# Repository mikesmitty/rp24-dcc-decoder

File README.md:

# rp24-dcc-decoder
DIY DCC decoder for model railroad locomotives in an E24 form factor suitable for N scale/gauge locomotives

[Decoder identifying to JMRI](https://www.youtube.com/watch?v=m5kexSfDo3k)

## Features
- 8x MOSFET-switched functions
- 5x GPIO pins (3.3V input/output)
- Up to 0.75A motor current
- E24 form factor (approx 20mm x 9mm)
- i2s audio speaker output
- 12V nominal rail voltage (16V max)

# USB Programmer/E24 Tester

- USB-C port for easy programming and loading sound files
- Onboard LEDs for all aux outputs for simple decoder testing
- Breakout header for most E24 pins, including speaker, motor, rectified rail power, Vcc, plus all five E24 GPIO pins (Aux 3, 4, 10, 11, 12)
- Programming track input header allows for stationary decoder testing and CV programming

# RP24 Decoder Pinout
| E24 Pin | Function | GPIO Pin |
| --- | --- | --- |
| 1 | Speaker- | USB D- |
| 2 | Speaker+ | USB D+ |
| 3 | GND | GND |
| 4-5 | Motor- | N/A |
| 6-7 | Motor+ | N/A |
| 8 | Cap+ | GPIO20 |
| 9 | Lamp Front | GPIO6 (MOSFET) |
| 10 | Lamp Rear | GPIO7 (MOSFET) |
| 11 | AUX1 | GPIO8 (MOSFET) |
| 12 | AUX2 | GPIO5 (MOSFET) |
| 13 | AUX8 | GPIO4 (MOSFET) |
| 14 | AUX7 | GPIO3 (MOSFET) |
| 15 | AUX6 | GPIO9 (MOSFET) |
| 16 | AUX5 | GPIO2 (MOSFET) |
| 17 | U+ | DC Rail Voltage |
| 18 | Vcc | 3.3V |
| 19 | AUX10 | GPIO10 |
| 20 | AUX4 | GPIO13 |
| 21 | AUX3 | GPIO14 |
| 22 | GND | GND |
| 23 | AUX11 | GPIO0 |
| 24 | AUX12 | GPIO1 |
| N/A | Motor Driver A | GPIO25 |
| N/A | Motor Driver B | GPIO26 |
| N/A | Back EMF A | GPIO28 |
| N/A | Back EMF B | GPIO29 |
| N/A | DCC signal Left Rail | GPIO21 |
| N/A | DCC signal Right Rail | GPIO27 |
| N/A | RailCom Out | GPIO11 |
| N/A | Status LED | GPIO19 |
| N/A | i2s DIN | GPIO22 |
| N/A | i2s BCLK | GPIO23 |
| N/A | i2s LRCLK | GPIO24 |
| N/A | Charge external keepalive capacitor (PWM at very low duty cycle only) | GPIO20 |

# E24 Receiver/Wire Breakout Board

## Receiver Board Solder Pads
| E24 Pin | Function | Label |
| --- | --- | --- |
| 1 | Speaker- | SPK |
| 2 | Speaker+ | SPK |
| 3 | GND | G |
| 4-5 | Motor- | - MOTOR + |
| 6-7 | Motor+ | - MOTOR + |
| 8 | External Capacitor+ | C |
| 9 | Lamp Front | F LAMP R |
| 10 | Lamp Rear | F LAMP R |
| 11 | AUX1 | 1 |
| 12 | AUX2 | 2 |
| 17 | DC Rail Voltage | RV |
| 18 | Microcontroller Voltage Output | Vcc |
| 19 | AUX10 | 10 |
| 20 | AUX4 | 4 |
| 21 | AUX3 | 3 |
| 22 | GND | G |
| 23 | AUX11 | 11 |
| 24 | AUX12 | 12 |

Inspired by the rp2040-decoder project by gab-k: https://github.com/gab-k/RP2040-Decoder

## Reference:
### E24
- RCD-124 (German): https://normen.railcommunity.de/RCD-124.pdf
- https://dccwiki.com/Locomotive_Interface/E24
### RailCom
- [NMRA S-9.3.2, Section 2](https://www.nmra.org/sites/default/files/s-9.3.2_2012_12_10.pdf)
- Example RailCom transmitter circuit: [CircuitJS](https://www.falstad.com/circuit/circuitjs.html?ctz=CQAgjCAMB0l3BWcMBMcUHYMGZIA4UA2ATmIxAUgoqoQFMBaMMAKABdkUAWEFbkYoSp8eVJr2h9CKBIS6E8kQrgyRsjPCAYZJM4vgxCU2E90bNecEABM6AMwCGAVwA2bdgMO8MKTj0y+YhDY0GB4XAgmkFwoYAhg0sRaKLrSsvKKypCq6gyaaFS2jq7uAE5+4EIVIlC8KCzlgsI+IHiC3oEgCnAsAEoVzL5gkPxcmlRUXFQh2LUT0Ageg9MIQ2E82Ku1EDDZxG1cU-FywwhJMMwI8iRoMXKr8paF9s5uSyMbW2SEIJudO7AMPtiIc0DIwAVsD9hFYiq8yhU-uAIStOt1ICwAMqtdoBECGfItKgQRwuADOdFq9QA5viFLw8JoCb8oXMWLTmOFfvTOTwphMoCxsKoKvIeMsQGLfmyAO7VfjDfgyaEsOVNXhTARVPEYtXalrfDqCuWK8UQrXE826i2VKjqtDjVU2wZ0zQu63Ml3M5XG6qMxFba2GqGaQ3831hqymyVWa3R8PRpFx9Ysn4Q7C+Ewqk3GTOs9O+KVB81S4jmrMR8us4OsuO5yVyZFoBuiJ3xxtlwuNjHC4kfJsDKqzCZO9UusdVDFAA)

View this project on [CADLAB.io](https://cadlab.io/project/28797).

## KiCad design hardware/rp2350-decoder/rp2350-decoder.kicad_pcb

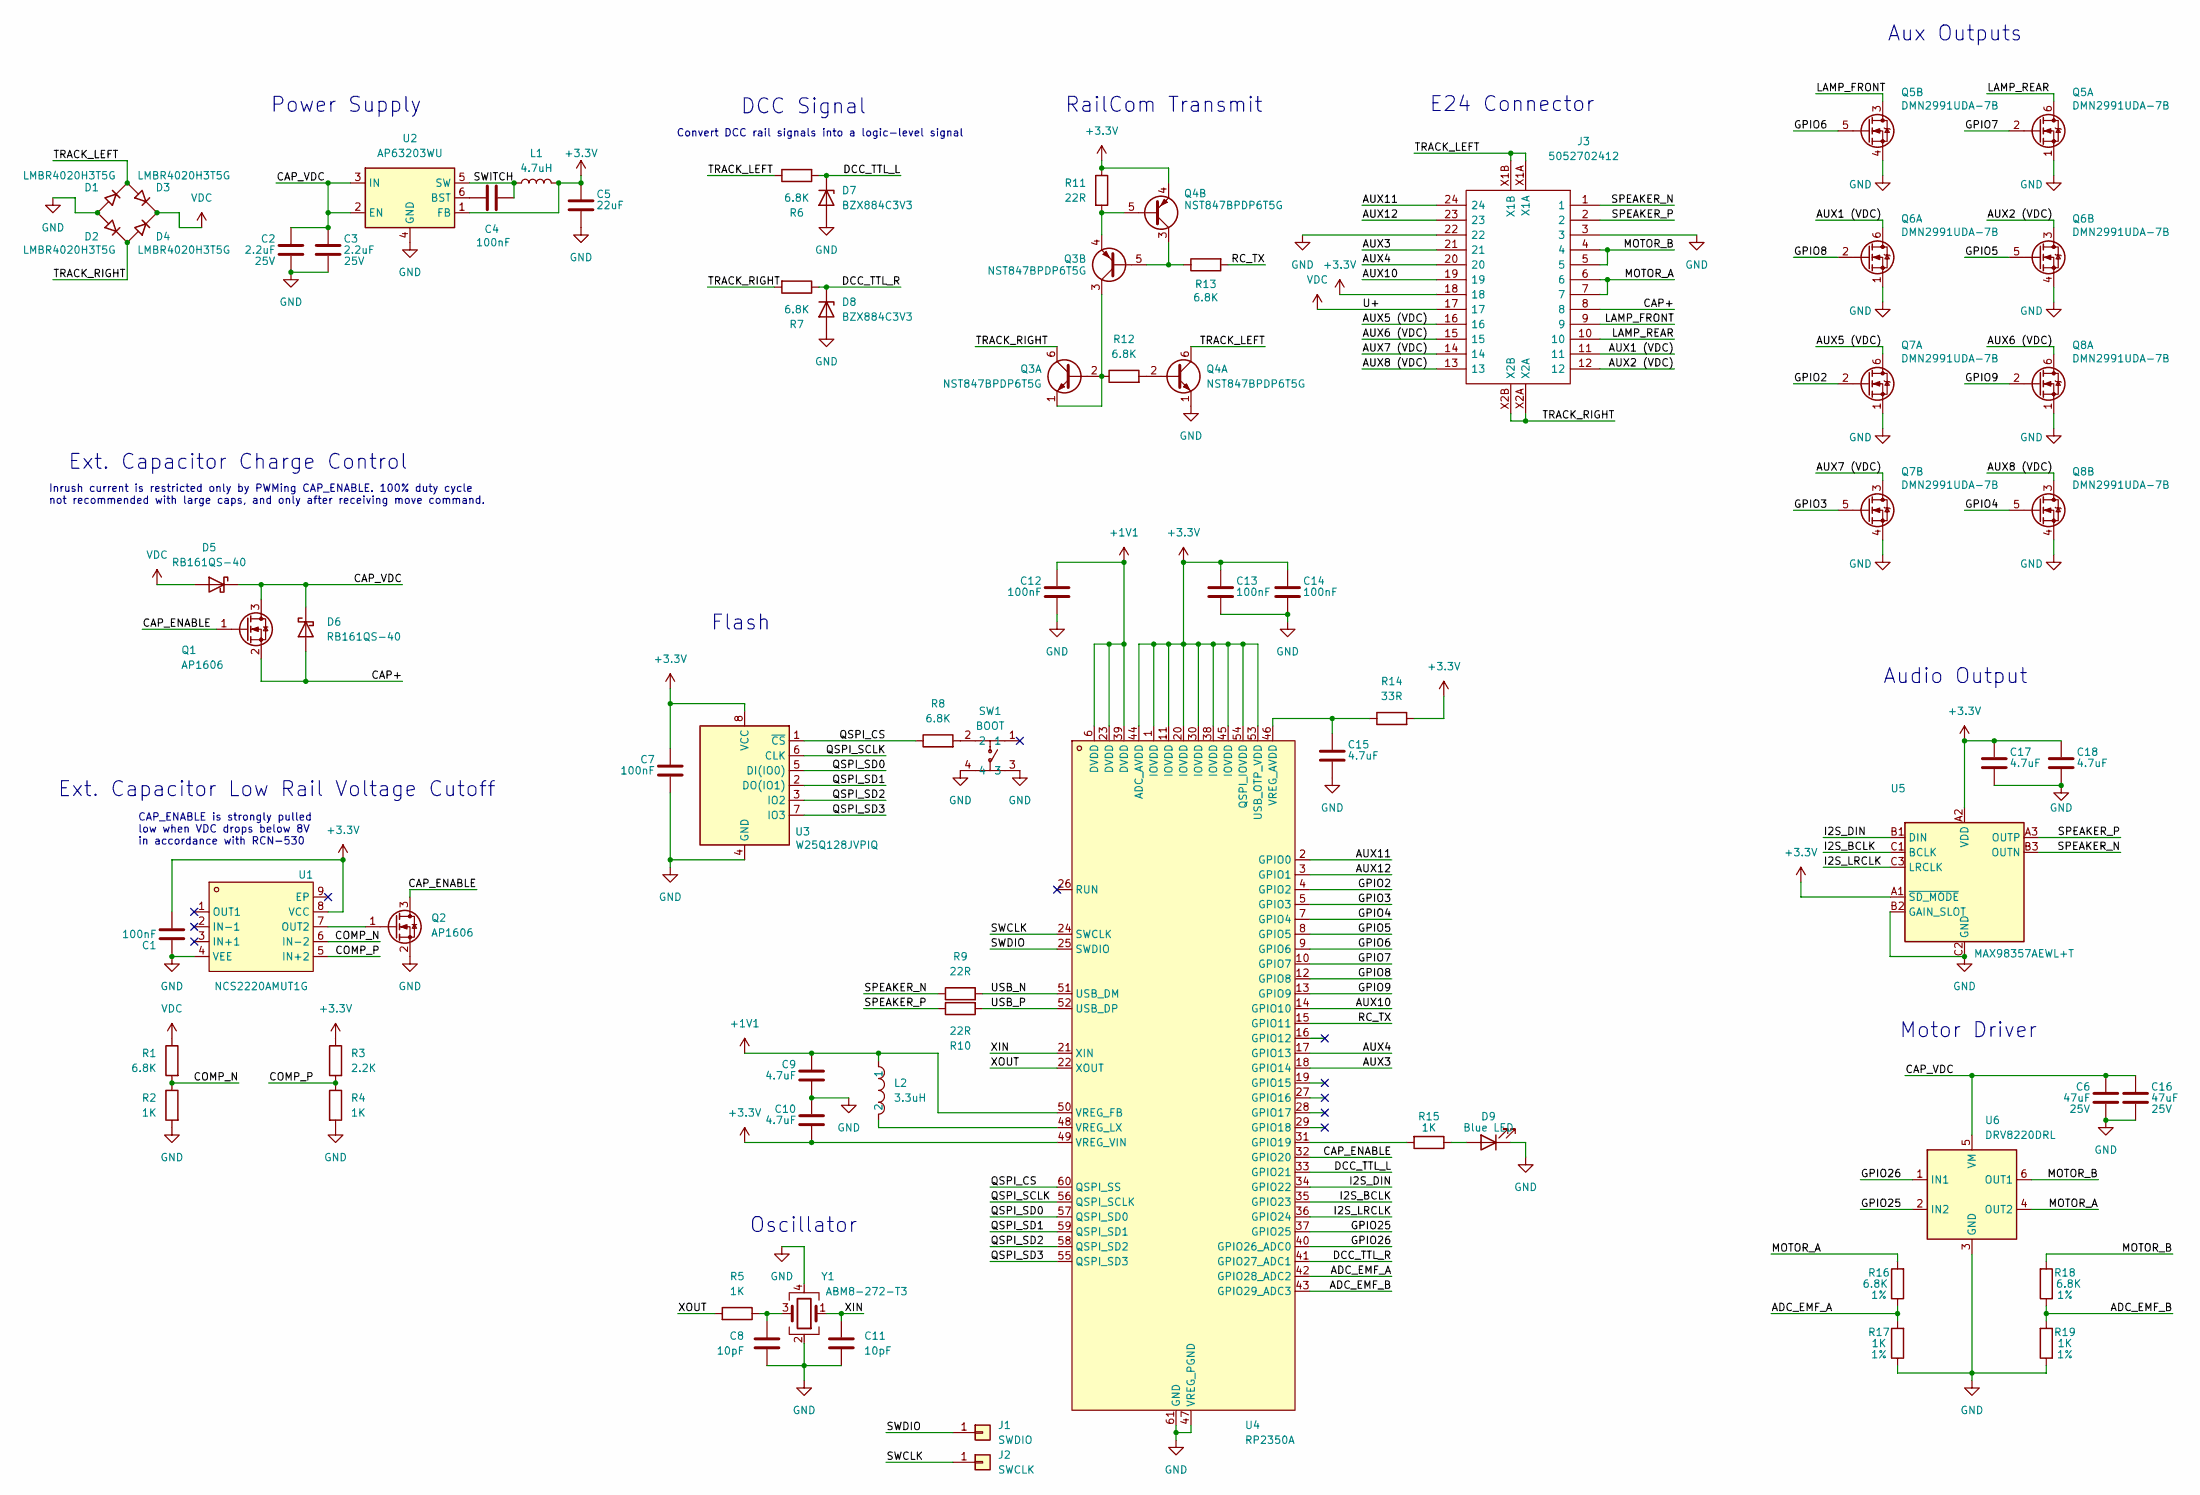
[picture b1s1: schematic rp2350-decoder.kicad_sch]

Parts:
C1, C4, C7, C12, C13, C14: 100nF; C_0201_0603Metric; LCSC C49062
C2, C3: 2.2uF; C_0402_1005Metric; Voltage 25V; LCSC C159814
C5: 22uF; C_0603_1608Metric; LCSC C86295
C6, C16: 47uF; C_1206_3216Metric; Voltage 25V; LCSC C22367835
C8, C11: 10pF; C_0201_0603Metric; LCSC C384956
C9, C10, C15, C17, C18: 4.7uF; C_0201_0603Metric; LCSC C335103
D1, D2, D3, D4: LMBR4020H3T5G; U-DFN1608-2_L1.6-W0.8-RD; LCSC C2852608
D5, D6: RB161QS-40; DIO-SMD_L1.0-W0.6-P0.65-RD; LCSC C5563750
D7, D8: BZX884C3V3; DFN1006-2L-RD; LCSC C7529009
D9: Blue LED; LED_0402_1005Metric; LCSC C130724
J1: SWDIO; Pogo Pad 0.8mm
J2: SWCLK; Pogo Pad 0.8mm
J3: 5052702412; CONN-SMD_5052702412; LCSC C724151
L1: 4.7uH; IND-SMD_L2.5-W2.0-VLS252012CX-150M; LCSC C5832360
L2: 3.3uH; L_pol_2016; LCSC C42411119
Q1, Q2: AP1606; Diodes_DFN1006-3; LCSC C2849580
Q3, Q4: NST847BPDP6T5G; SOT-963; LCSC C896443
Q5, Q6, Q7, Q8: DMN2991UDA-7B; X2-DFN0806-6_L0.8-W0.6_X2-DFN0806-6; LCSC C2937136
R1, R6, R7, R8, R12, R13: 6.8K; R_0201_0603Metric; LCSC C423451
R2, R4, R5, R15: 1K; R_0201_0603Metric; LCSC C270365
R3: 2.2K; R_0201_0603Metric; LCSC C473534
R9, R10, R11: 22R; R_0201_0603Metric; LCSC C270355
R14: 33R; R_0201_0603Metric; LCSC C423356
R16, R18: 6.8K; R_0201_0603Metric; Tolerance 1%; LCSC C423451
R17, R19: 1K; R_0201_0603Metric; Tolerance 1%; LCSC C270365
SW1: BOOT; SW-SMD_4P-L2.6-W1.6-P0.75-LS3.0; LCSC C913778
U1: NCS2220AMUT1G; DFN-8_L1.6-W1.6-P0.40-BL-EP; LCSC C464059
U2: AP63203WU; TSOT-26_L2.9-W1.6-P0.95-LS2.8-BL; LCSC C780769
U3: W25Q128JVPIQ; WSON-8-1EP_6x5mm_P1.27mm_EP3.4x4.3mm; LCSC C190862
U4: RP2350A; QFN-60_L7.0-W7.0-P0.40-TL-EP3.4; LCSC C42411118
U5: MAX98357AEWL+T; WLP-9_L1.4-W1.3-P0.40-R3-C3-BR; LCSC C2682619
U6: DRV8220DRL; SOT-563; LCSC C3681351
Y1: ABM8-272-T3; Crystal_SMD_3225-4Pin_3.2x2.5mm; LCSC C20625731

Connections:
+1V1: C9.1, C12.1, L2.1, U4.6 (DVDD), U4.23 (DVDD), U4.39 (DVDD), U4.50 (VREG_FB)
+3.3V: C1.2, C5.1, C7.1, C10.2, C13.1, C14.1, C17.1, C18.1, J3.18, L1.2, Q4.4 (E2), R3.1, R11.1, R14.2, U1.8 (VCC), U2.1 (FB), U3.8 (VCC), U4.1 (IOVDD), U4.11 (IOVDD), U4.20 (IOVDD), U4.30 (IOVDD), U4.38 (IOVDD), U4.44 (ADC_AVDD), U4.45 (IOVDD), U4.49 (VREG_VIN), U4.53 (USB_OTP_VDD), U4.54 (QSPI_IOVDD), U5.A1 (~SD_MODE), U5.A2 (VDD)
/ADC_EMF_A: R16.1, R17.2, U4.42 (GPIO28_ADC2)
/ADC_EMF_B: R18.1, R19.2, U4.43 (GPIO29_ADC3)
/AUX1 (VDC): J3.11, Q6.6 (D1)
/AUX2 (VDC): J3.12, Q6.3 (D2)
/AUX3: J3.21, U4.18 (GPIO14)
/AUX4: J3.20, U4.17 (GPIO13)
/AUX5 (VDC): J3.16, Q7.6 (D1)
/AUX6 (VDC): J3.15, Q8.6 (D1)
/AUX7 (VDC): J3.14, Q7.3 (D2)
/AUX8 (VDC): J3.13, Q8.3 (D2)
/AUX10: J3.19, U4.14 (GPIO10)
/AUX11: J3.24, U4.2 (GPIO0)
/AUX12: J3.23, U4.3 (GPIO1)
/CAP+: D6.2 (A), J3.8, Q1.2 (S)
/CAP_ENABLE: Q1.1 (G), Q2.3 (D), U4.32 (GPIO20)
/CAP_VDC: C2.1, C3.1, C6.1, C16.1, D5.1 (K), D6.1 (K), Q1.3 (D), U2.2 (EN), U2.3 (IN), U6.5 (VM)
/COMP_N: R1.2, R2.1, U1.6 (IN−2)
/COMP_P: R3.2, R4.1, U1.5 (IN+2)
/DCC_TTL_L: D7.1 (K), R6.2, U4.33 (GPIO21)
/DCC_TTL_R: D8.1 (K), R7.1, U4.41 (GPIO27_ADC1)
/GPIO2: Q7.2 (G1), U4.4 (GPIO2)
/GPIO3: Q7.5 (G2), U4.5 (GPIO3)
/GPIO4: Q8.5 (G2), U4.7 (GPIO4)
/GPIO5: Q6.5 (G2), U4.8 (GPIO5)
/GPIO6: Q5.5 (G2), U4.9 (GPIO6)
/GPIO7: Q5.2 (G1), U4.10 (GPIO7)
/GPIO8: Q6.2 (G1), U4.12 (GPIO8)
/GPIO9: Q8.2 (G1), U4.13 (GPIO9)
/GPIO25: U4.37 (GPIO25), U6.2 (IN2)
/GPIO26: U4.40 (GPIO26_ADC0), U6.1 (IN1)
/I2S_BCLK: U4.35 (GPIO23), U5.C1 (BCLK)
/I2S_DIN: U4.34 (GPIO22), U5.B1 (DIN)
/I2S_LRCLK: U4.36 (GPIO24), U5.C3 (LRCLK)
/LAMP_FRONT: J3.9, Q5.3 (D2)
/LAMP_REAR: J3.10, Q5.6 (D1)
/MOTOR_A: J3.6, J3.7, R16.2, U6.4 (OUT2)
/MOTOR_B: J3.4, J3.5, R18.2, U6.6 (OUT1)
/QSPI_CS: R8.1, U3.1 (~CS), U4.60 (QSPI_SS)
/QSPI_SCLK: U3.6 (CLK), U4.56 (QSPI_SCLK)
/QSPI_SD0: U3.5 (DI(IO0)), U4.57 (QSPI_SD0)
/QSPI_SD1: U3.2 (DO(IO1)), U4.59 (QSPI_SD1)
/QSPI_SD2: U3.3 (IO2), U4.58 (QSPI_SD2)
/QSPI_SD3: U3.7 (IO3), U4.55 (QSPI_SD3)
/RC_TX: R13.2, U4.15 (GPIO11)
/SPEAKER_N: J3.1, R9.1, U5.B3 (OUTN)
/SPEAKER_P: J3.2, R10.1, U5.A3 (OUTP)
/SWCLK: J2.1, U4.24 (SWCLK)
/SWDIO: J1.1, U4.25 (SWDIO)
/SWITCH: C4.2, L1.1, U2.5 (SW)
/TRACK_LEFT: D1.1 (K), D3.2 (A), J3.X1A, J3.X1B, Q4.6 (C1), R6.1
/TRACK_RIGHT: D2.1 (K), D4.2 (A), J3.X2A, J3.X2B, Q3.6 (C1), R7.2
/USB_N: R9.2, U4.51 (USB_DM)
/USB_P: R10.2, U4.52 (USB_DP)
/XIN: C11.1, U4.21 (XIN), Y1.1
/XOUT: R5.2, U4.22 (XOUT)
GND: C1.1, C2.2, C3.2, C5.2, C6.2, C7.2, C8.2, C9.2, C10.1, C11.2, C12.2, C13.2, C14.2, C15.2, C16.2, C17.2, C18.2, D1.2 (A), D2.2 (A), D7.2 (A), D8.2 (A), D9.1 (K), J3.3, J3.22, Q2.2 (S), Q4.1 (E1), Q5.1 (S1), Q5.4 (S2), Q6.1 (S1), Q6.4 (S2), Q7.1 (S1), Q7.4 (S2), Q8.1 (S1), Q8.4 (S2), R2.2, R4.2, R17.1, R19.1, SW1.3, SW1.4, U1.4 (VEE), U2.4 (GND), U3.4 (GND), U3.9 (GND), U4.47 (VREG_PGND), U4.61 (GND), U5.B2 (GAIN_SLOT), U5.C2 (GND), U6.3 (GND), Y1.2, Y1.4
unnamed: C8.1, R5.1, Y1.3
unnamed: D9.2 (A), R15.1
unnamed: Q2.1 (G), U1.7 (OUT2)
unnamed: Q3.1 (E1), Q3.2 (B1), Q3.3 (C2), R12.1
unnamed: Q3.5 (B2), Q4.3 (C2), R13.1
unnamed: Q3.4 (E2), Q4.5 (B2), R11.2
unnamed: Q4.2 (B1), R12.2
unnamed: R8.2, SW1.2
unnamed: C4.1, U2.6 (BST)
unnamed: R15.2, U4.31 (GPIO19)
unnamed: C15.1, R14.1, U4.46 (VREG_AVDD)
unnamed: L2.2, U4.48 (VREG_LX)
VDC: D3.1 (K), D4.1 (K), D5.2 (A), J3.17, R1.1

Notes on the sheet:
Inrush current is restricted only by PWMing CAP_ENABLE. 100% duty cycle not recommended with large caps, and only after receiving move command.
CAP_ENABLE is strongly pulled low when VDC drops below 8V in accordance with RCN-530
Aux Outputs
RailCom Transmit
Convert DCC rail signals into a logic-level signal
Motor Driver
Oscillator
Power Supply
Flash
Ext. Capacitor Low Rail Voltage Cutoff
Ext. Capacitor Charge Control
Audio Output
E24 Connector
DCC Signal

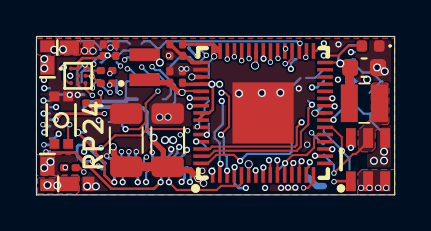
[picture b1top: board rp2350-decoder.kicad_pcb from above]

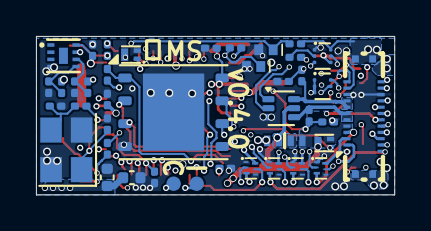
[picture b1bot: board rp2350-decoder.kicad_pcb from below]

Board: 6 copper layers, 19.9 x 8.8 mm, 67 parts (43 on the bottom side), 71 nets.

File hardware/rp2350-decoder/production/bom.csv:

Comment,Designator,Footprint,LCSC
LMBR4020H3T5G,"D1,D2,D3,D4",rp2350-decoder:U-DFN1608-2_L1.6-W0.8-RD,C2852608
MAX98357AEWL+T,U5,rp2350-decoder:WLP-9_L1.4-W1.3-P0.40-R3-C3-BR,C2682619
100nF,"C1,C4,C7,C12,C13,C14,C19",rp2350-decoder:C_0201_0603Metric,C49062
1K,"R2,R4,R5,R15,R17,R19",rp2350-decoder:R_0201_0603Metric,C270365
6.8K,"R1,R6,R7,R8,R12,R13,R16,R18",rp2350-decoder:R_0201_0603Metric,C423451
AP63203WU,U2,rp2350-decoder:TSOT-26_L2.9-W1.6-P0.95-LS2.8-BL,C780769
AP1606,"Q1,Q2",rp2350-decoder:Diodes_DFN1006-3,C2849580
BZX884C3V3,"D7,D8",rp2350-decoder:DFN1006-2L-RD,C7529009
NST847BPDP6T5G,"Q3,Q4",rp2350-decoder:SOT-963,C896443
BOOT,SW1,rp2350-decoder:SW-SMD_4P-L2.6-W1.6-P0.75-LS3.0,C913778
22R,"R9,R10,R11",rp2350-decoder:R_0201_0603Metric,C270355
2.2K,R3,rp2350-decoder:R_0201_0603Metric,C473534
DMN2991UDA-7B,"Q5,Q6,Q7,Q8",rp2350-decoder:X2-DFN0806-6_L0.8-W0.6_X2-DFN0806-6,C2937136
3.3uH,L2,rp2350-decoder:L_pol_2016,C42411119
4.7uF,"C9,C10,C15,C17,C18",rp2350-decoder:C_0201_0603Metric,C335103
RB161QS-40,"D5,D6",rp2350-decoder:DIO-SMD_L1.0-W0.6-P0.65-RD,C5563750
MD9927,U6,rp2350-decoder:WDFN-8_L2.0-W2.0-P0.50-BL-EP,C2684662
47uF,C16,rp2350-decoder:C_1206_3216Metric,C22367835
10pF,"C8,C11",rp2350-decoder:C_0201_0603Metric,C384956
5052702412,J3,rp2350-decoder:CONN-SMD_5052702412,C724151
W25Q128JVPIQ,U3,rp2350-decoder:WSON-8-1EP_6x5mm_P1.27mm_EP3.4x4.3mm,C190862
4.7uH,L1,rp2350-decoder:IND-SMD_L2.5-W2.0-VLS252012CX-150M,C5832360
ABM8-272-T3,Y1,rp2350-decoder:Crystal_SMD_3225-4Pin_3.2x2.5mm,C20625731
NCS2220AMUT1G,U1,rp2350-decoder:DFN-8_L1.6-W1.6-P0.40-BL-EP,C464059
2.2uF,"C2,C3",rp2350-decoder:C_0402_1005Metric,C159814
100uF,C6,rp2350-decoder:C_1206_3216Metric,C15008
33R,R14,rp2350-decoder:R_0201_0603Metric,C423356
Blue LED,D9,rp2350-decoder:LED_0402_1005Metric,C130724
RP2350A,U4,rp2350-decoder:QFN-60_L7.0-W7.0-P0.40-TL-EP3.4,C42411118
22uF,C5,rp2350-decoder:C_0603_1608Metric,C86295

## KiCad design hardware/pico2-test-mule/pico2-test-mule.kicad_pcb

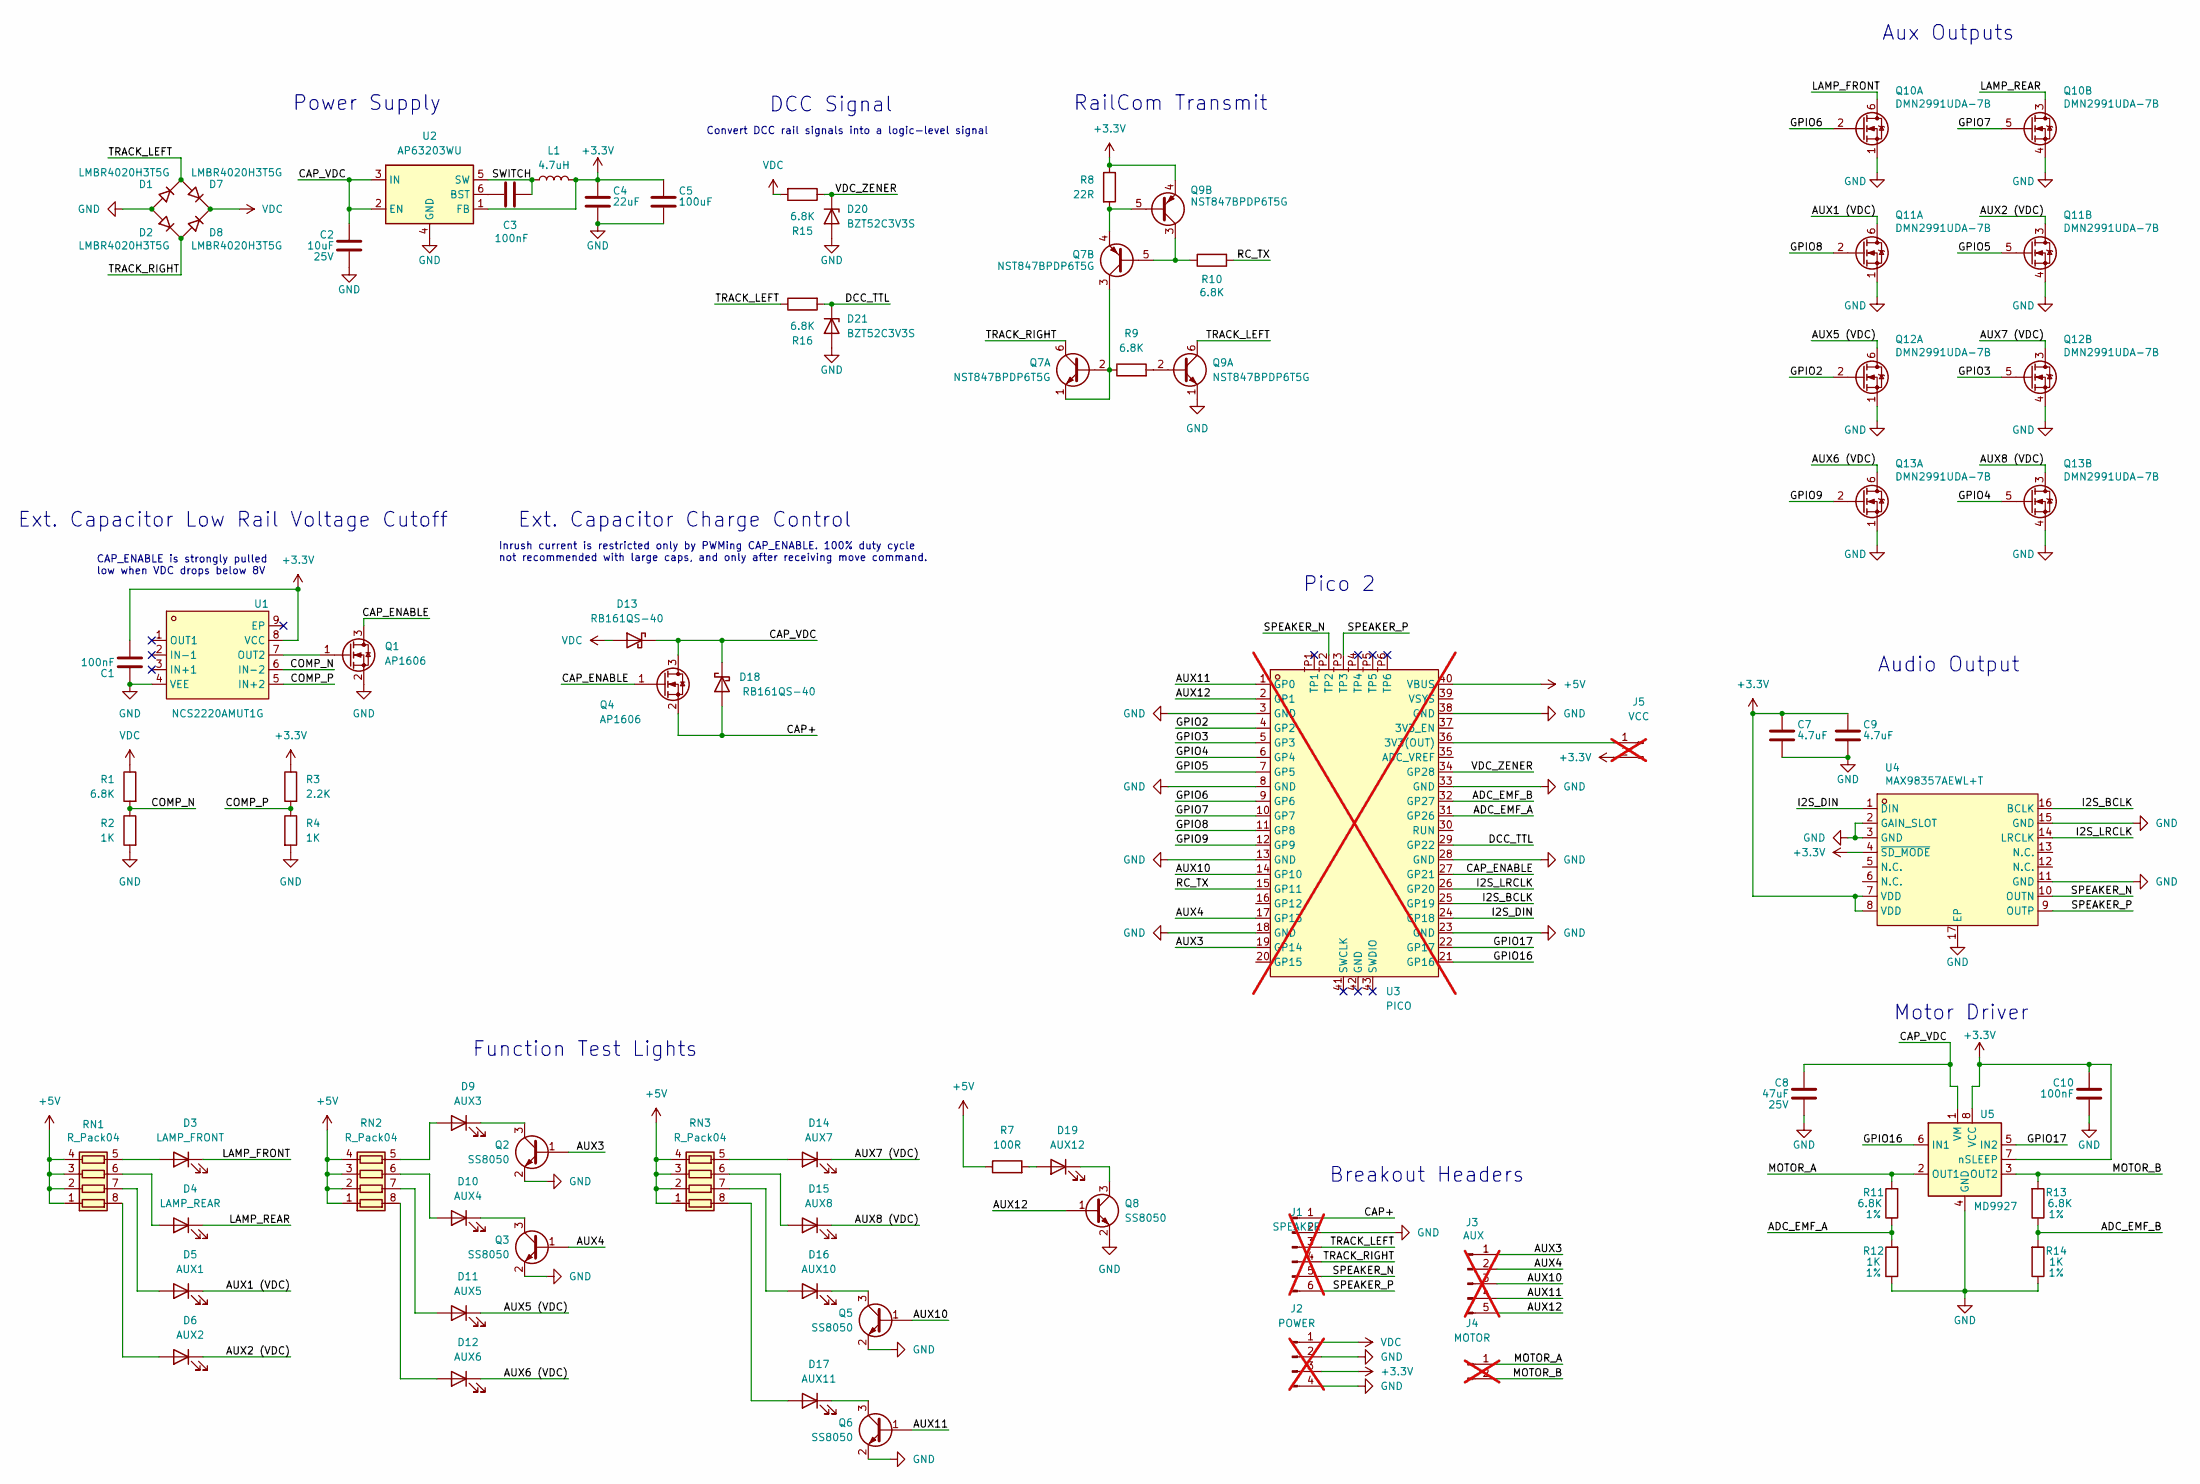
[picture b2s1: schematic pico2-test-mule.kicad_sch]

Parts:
C1, C3, C10: 100nF; C_0402_1005Metric; LCSC C1525
C2: 10uF; C_0603_1608Metric; Voltage 25V; LCSC C96446
C4: 22uF; C_0603_1608Metric; LCSC C86295
C5: 100uF; C_1206_3216Metric; LCSC C15008
C7, C9: 4.7uF; C_0402_1005Metric; LCSC C307423
C8: 47uF; C_1206_3216Metric; Voltage 25V; LCSC C22367835
D1, D2, D7, D8: LMBR4020H3T5G; U-DFN1608-2_L1.6-W0.8-RD; LCSC C2852608
D3: LAMP_FRONT; LED_0603_1608Metric; LCSC C2290
D4: LAMP_REAR; LED_0603_1608Metric; LCSC C2290
D5: AUX1; LED_0603_1608Metric; LCSC C2290
D6: AUX2; LED_0603_1608Metric; LCSC C2290
D9: AUX3; LED_0603_1608Metric; LCSC C2290
D10: AUX4; LED_0603_1608Metric; LCSC C2290
D11: AUX5; LED_0603_1608Metric; LCSC C2290
D12: AUX6; LED_0603_1608Metric; LCSC C2290
D13, D18: RB161QS-40; DIO-SMD_L1.0-W0.6-P0.65-RD; LCSC C5563750
D14: AUX7; LED_0603_1608Metric; LCSC C2290
D15: AUX8; LED_0603_1608Metric; LCSC C2290
D16: AUX10; LED_0603_1608Metric; LCSC C2290
D17: AUX11; LED_0603_1608Metric; LCSC C2290
D19: AUX12; LED_0603_1608Metric; LCSC C2290
D20, D21: BZT52C3V3S; D_SOD-323; LCSC C19077437
J1: SPEAKER; PinHeader_1x06_P2.54mm_Vertical; not fitted
J2: POWER; PinHeader_1x04_P2.54mm_Vertical; not fitted
J3: AUX; PinHeader_1x05_P2.54mm_Vertical; not fitted
J4: MOTOR; PinHeader_1x02_P2.54mm_Vertical; not fitted
J5: VCC; PinHeader_1x02_P2.54mm_Vertical; not fitted
L1: 4.7uH; IND-SMD_L2.5-W2.0-VLS252012CX-150M; LCSC C5832360
Q1, Q4: AP1606; Diodes_DFN1006-3; LCSC C2849580
Q2, Q3, Q5, Q6, Q8: SS8050; SOT-23; LCSC C2150
Q7, Q9: NST847BPDP6T5G; SOT-963; LCSC C896443
Q10, Q11, Q12, Q13: DMN2991UDA-7B; X2-DFN0806-6_L0.8-W0.6_X2-DFN0806-6; LCSC C2937136
R1, R9, R10, R15, R16: 6.8K; R_0402_1005Metric; LCSC C25944
R2, R4: 1K; R_0402_1005Metric; LCSC C11702
R3: 2.2K; R_0402_1005Metric; LCSC C25879
R7: 100R; R_0402_1005Metric; LCSC C25076
R8: 22R; R_0402_1005Metric; LCSC C25092
R11, R13: 6.8K; R_0402_1005Metric; Tolerance 1%; LCSC C25944
R12, R14: 1K; R_0402_1005Metric; Tolerance 1%; LCSC C11702
RN1, RN2, RN3: R_Pack04; R_Array_Concave_4x0402; LCSC C48442
U1: NCS2220AMUT1G; DFN-8_L1.6-W1.6-P0.40-BL-EP; LCSC C464059
U2: AP63203WU; TSOT-26_L2.9-W1.6-P0.95-LS2.8-BL; LCSC C780769
U3: PICO; RaspberryPi_Pico_Common_THT; not fitted
U4: MAX98357AEWL+T; TQFN-16_L3.0-W3.0-P0.50-BL-EP1.5; LCSC C910544
U5: MD9927; WDFN-8_L2.0-W2.0-P0.50-BL-EP; LCSC C2684662

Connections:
+3.3V: C1.2, C4.1, C5.1, C7.1, C9.1, C10.1, J2.3, J5.2, L1.2, Q9.4 (E2), R3.1, R8.1, U1.8 (VCC), U2.1 (FB), U4.4 (~SD_MODE), U4.7 (VDD), U4.8 (VDD), U5.7 (nSLEEP), U5.8 (VCC)
+5V: R7.1, RN1.1 (R1.1), RN1.2 (R2.1), RN1.3 (R3.1), RN1.4 (R4.1), RN2.1 (R1.1), RN2.2 (R2.1), RN2.3 (R3.1), RN2.4 (R4.1), RN3.1 (R1.1), RN3.2 (R2.1), RN3.3 (R3.1), RN3.4 (R4.1), U3.40 (VBUS)
/ADC_EMF_A: R11.1, R12.2, U3.31 (GP26)
/ADC_EMF_B: R13.1, R14.2, U3.32 (GP27)
/AUX1 (VDC): D5.1 (K), Q11.6 (D1)
/AUX2 (VDC): D6.1 (K), Q11.3 (D2)
/AUX3: J3.1, Q2.1 (B), U3.19 (GP14)
/AUX4: J3.2, Q3.1 (B), U3.17 (GP13)
/AUX5 (VDC): D11.1 (K), Q12.6 (D1)
/AUX6 (VDC): D12.1 (K), Q13.6 (D1)
/AUX7 (VDC): D14.1 (K), Q12.3 (D2)
/AUX8 (VDC): D15.1 (K), Q13.3 (D2)
/AUX10: J3.3, Q5.1 (B), U3.14 (GP10)
/AUX11: J3.4, Q6.1 (B), U3.1 (GP0)
/AUX12: J3.5, Q8.1 (B), U3.2 (GP1)
/CAP+: D18.2 (A), J1.1, Q4.2 (S)
/CAP_ENABLE: Q1.3 (D), Q4.1 (G), U3.27 (GP21)
/CAP_VDC: C2.1, C8.1, D13.1 (K), D18.1 (K), Q4.3 (D), U2.2 (EN), U2.3 (IN), U5.1 (VM)
/COMP_N: R1.2, R2.1, U1.6 (IN−2)
/COMP_P: R3.2, R4.1, U1.5 (IN+2)
/DCC_TTL: D21.1 (K), R16.2, U3.29 (GP22)
/GPIO2: Q12.2 (G1), U3.4 (GP2)
/GPIO3: Q12.5 (G2), U3.5 (GP3)
/GPIO4: Q13.5 (G2), U3.6 (GP4)
/GPIO5: Q11.5 (G2), U3.7 (GP5)
/GPIO6: Q10.2 (G1), U3.9 (GP6)
/GPIO7: Q10.5 (G2), U3.10 (GP7)
/GPIO8: Q11.2 (G1), U3.11 (GP8)
/GPIO9: Q13.2 (G1), U3.12 (GP9)
/GPIO16: U3.21 (GP16), U5.6 (IN1)
/GPIO17: U3.22 (GP17), U5.5 (IN2)
/I2S_BCLK: U3.25 (GP19), U4.16 (BCLK)
/I2S_DIN: U3.24 (GP18), U4.1 (DIN)
/I2S_LRCLK: U3.26 (GP20), U4.14 (LRCLK)
/LAMP_FRONT: D3.1 (K), Q10.6 (D1)
/LAMP_REAR: D4.1 (K), Q10.3 (D2)
/MOTOR_A: J4.1, R11.2, U5.2 (OUT1)
/MOTOR_B: J4.2, R13.2, U5.3 (OUT2)
/RC_TX: R10.2, U3.15 (GP11)
/SPEAKER_N: J1.5, U3.TP2, U4.10 (OUTN)
/SPEAKER_P: J1.6, U3.TP3, U4.9 (OUTP)
/SWITCH: C3.2, L1.1, U2.5 (SW)
/TRACK_LEFT: D1.1 (K), D7.2 (A), J1.3, Q9.6 (C1), R16.1
/TRACK_RIGHT: D2.1 (K), D8.2 (A), J1.4, Q7.6 (C1)
/VDC_ZENER: D20.1 (K), R15.1, U3.34 (GP28)
GND: C1.1, C2.2, C4.2, C5.2, C7.2, C8.2, C9.2, C10.2, D1.2 (A), D2.2 (A), D20.2 (A), D21.2 (A), J1.2, J2.2, J2.4, Q1.2 (S), Q2.2 (E), Q3.2 (E), Q5.2 (E), Q6.2 (E), Q8.2 (E), Q9.1 (E1), Q10.1 (S1), Q10.4 (S2), Q11.1 (S1), Q11.4 (S2), Q12.1 (S1), Q12.4 (S2), Q13.1 (S1), Q13.4 (S2), R2.2, R4.2, R12.1, R14.1, U1.4 (VEE), U2.4 (GND), U3.3 (GND), U3.8 (GND), U3.13 (GND), U3.18 (GND), U3.23 (GND), U3.28 (GND), U3.33 (GND), U3.38 (GND), U4.2 (GAIN_SLOT), U4.3 (GND), U4.11 (GND), U4.15 (GND), U4.17 (EP), U5.4 (GND), U5.9 (GND)
unnamed: D3.2 (A), RN1.5 (R4.2)
unnamed: D4.2 (A), RN1.6 (R3.2)
unnamed: D5.2 (A), RN1.7 (R2.2)
unnamed: D6.2 (A), RN1.8 (R1.2)
unnamed: D9.2 (A), RN2.5 (R4.2)
unnamed: D9.1 (K), Q2.3 (C)
unnamed: D10.2 (A), RN2.6 (R3.2)
unnamed: D10.1 (K), Q3.3 (C)
unnamed: D11.2 (A), RN2.7 (R2.2)
unnamed: D12.2 (A), RN2.8 (R1.2)
unnamed: D14.2 (A), RN3.5 (R4.2)
unnamed: D15.2 (A), RN3.6 (R3.2)
unnamed: D16.2 (A), RN3.7 (R2.2)
unnamed: D16.1 (K), Q5.3 (C)
unnamed: D17.2 (A), RN3.8 (R1.2)
unnamed: D17.1 (K), Q6.3 (C)
unnamed: D19.2 (A), R7.2
unnamed: D19.1 (K), Q8.3 (C)
unnamed: J5.1, U3.36 (3V3(OUT))
unnamed: Q1.1 (G), U1.7 (OUT2)
unnamed: Q7.1 (E1), Q7.2 (B1), Q7.3 (C2), R9.1
unnamed: Q7.5 (B2), Q9.3 (C2), R10.1
unnamed: Q7.4 (E2), Q9.5 (B2), R8.2
unnamed: Q9.2 (B1), R9.2
unnamed: C3.1, U2.6 (BST)
VDC: D7.1 (K), D8.1 (K), D13.2 (A), J2.1, R1.1, R15.2

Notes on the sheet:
Motor Driver
Ext. Capacitor Charge Control
Convert DCC rail signals into a logic-level signal
Audio Output
RailCom Transmit
DCC Signal
Aux Outputs
Function Test Lights
Ext. Capacitor Low Rail Voltage Cutoff
Power Supply
Pico 2
CAP_ENABLE is strongly pulled low when VDC drops below 8V
Inrush current is restricted only by PWMing CAP_ENABLE. 100% duty cycle not recommended with large caps, and only after receiving move command.
Breakout Headers

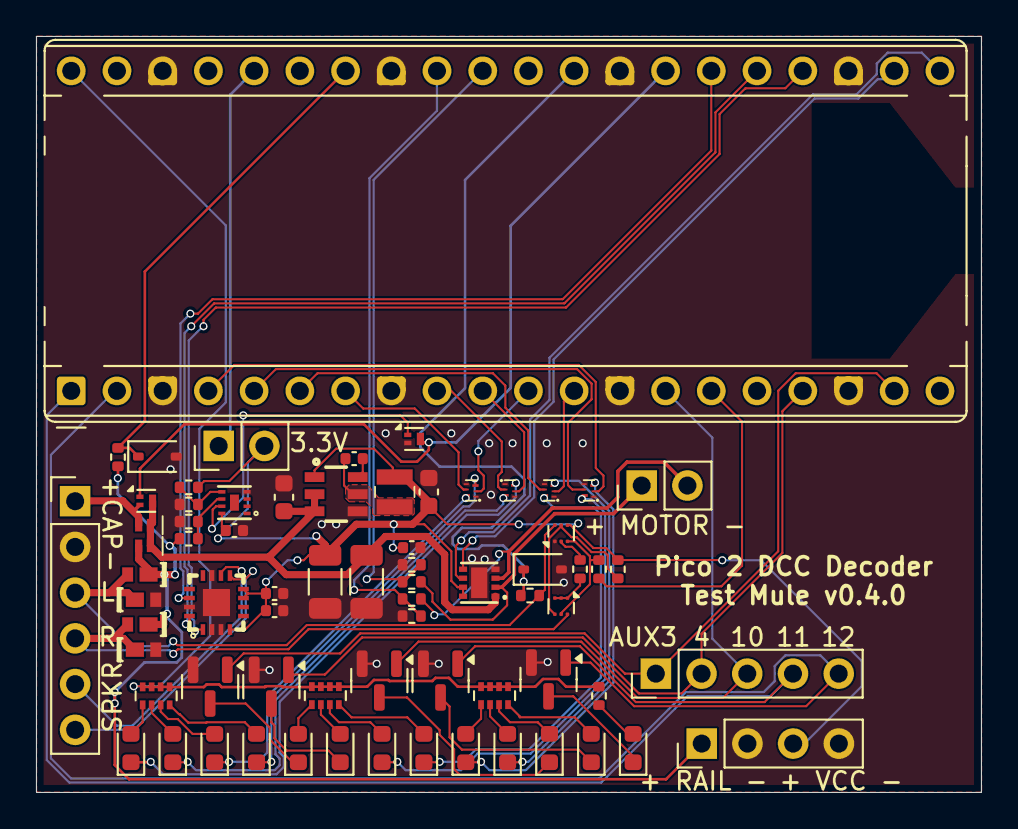
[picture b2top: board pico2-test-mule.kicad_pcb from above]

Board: 2 copper layers, 52.5 x 42.0 mm, 71 parts (0 on the bottom side), 72 nets.

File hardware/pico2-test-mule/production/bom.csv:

Comment,Designator,Footprint,LCSC
6.8K,"R1,R9,R10,R11,R13,R15,R16",pico2-test-mule:R_0402_1005Metric,C25944
100uF,C5,pico2-test-mule:C_1206_3216Metric,C15008
SS8050,"Q2,Q3,Q5,Q6,Q8",pico2-test-mule:SOT-23,C2150
AUX12,D19,pico2-test-mule:LED_0603_1608Metric,C2290
MAX98357AEWL+T,U4,pico2-test-mule:TQFN-16_L3.0-W3.0-P0.50-BL-EP1.5,C910544
1K,"R2,R4,R12,R14",pico2-test-mule:R_0402_1005Metric,C11702
DMN2991UDA-7B,"Q10,Q11,Q12,Q13",pico2-test-mule:X2-DFN0806-6_L0.8-W0.6_X2-DFN0806-6,C2937136
100nF,"C1,C3,C10",pico2-test-mule:C_0402_1005Metric,C1525
LMBR4020H3T5G,"D1,D2,D7,D8",pico2-test-mule:U-DFN1608-2_L1.6-W0.8-RD,C2852608
4.7uF,"C7,C9",pico2-test-mule:C_0402_1005Metric,C307423
AP1606,"Q1,Q4",pico2-test-mule:Diodes_DFN1006-3,C2849580
R_Pack04,"RN1,RN2,RN3",pico2-test-mule:R_Array_Concave_4x0402,C48442
BZT52C3V3S,"D20,D21",pico2-test-mule:D_SOD-323,C19077437
AUX10,D16,pico2-test-mule:LED_0603_1608Metric,C2290
4.7uH,L1,pico2-test-mule:IND-SMD_L2.5-W2.0-VLS252012CX-150M,C5832360
AUX1,D5,pico2-test-mule:LED_0603_1608Metric,C2290
MD9927,U5,pico2-test-mule:WDFN-8_L2.0-W2.0-P0.50-BL-EP,C2684662
AUX2,D6,pico2-test-mule:LED_0603_1608Metric,C2290
AUX7,D14,pico2-test-mule:LED_0603_1608Metric,C2290
22R,R8,pico2-test-mule:R_0402_1005Metric,C25092
NCS2220AMUT1G,U1,pico2-test-mule:DFN-8_L1.6-W1.6-P0.40-BL-EP,C464059
100R,R7,pico2-test-mule:R_0402_1005Metric,C25076
NST847BPDP6T5G,"Q7,Q9",pico2-test-mule:SOT-963,C896443
AP63203WU,U2,pico2-test-mule:TSOT-26_L2.9-W1.6-P0.95-LS2.8-BL,C780769
AUX8,D15,pico2-test-mule:LED_0603_1608Metric,C2290
10uF,C2,pico2-test-mule:C_0603_1608Metric,C96446
AUX6,D12,pico2-test-mule:LED_0603_1608Metric,C2290
2.2K,R3,pico2-test-mule:R_0402_1005Metric,C25879
47uF,C8,pico2-test-mule:C_1206_3216Metric,C22367835
22uF,C4,pico2-test-mule:C_0603_1608Metric,C86295
AUX3,D9,pico2-test-mule:LED_0603_1608Metric,C2290
RB161QS-40,"D13,D18",pico2-test-mule:DIO-SMD_L1.0-W0.6-P0.65-RD,C5563750
AUX4,D10,pico2-test-mule:LED_0603_1608Metric,C2290
LAMP_FRONT,D3,pico2-test-mule:LED_0603_1608Metric,C2290
LAMP_REAR,D4,pico2-test-mule:LED_0603_1608Metric,C2290
AUX5,D11,pico2-test-mule:LED_0603_1608Metric,C2290
AUX11,D17,pico2-test-mule:LED_0603_1608Metric,C2290

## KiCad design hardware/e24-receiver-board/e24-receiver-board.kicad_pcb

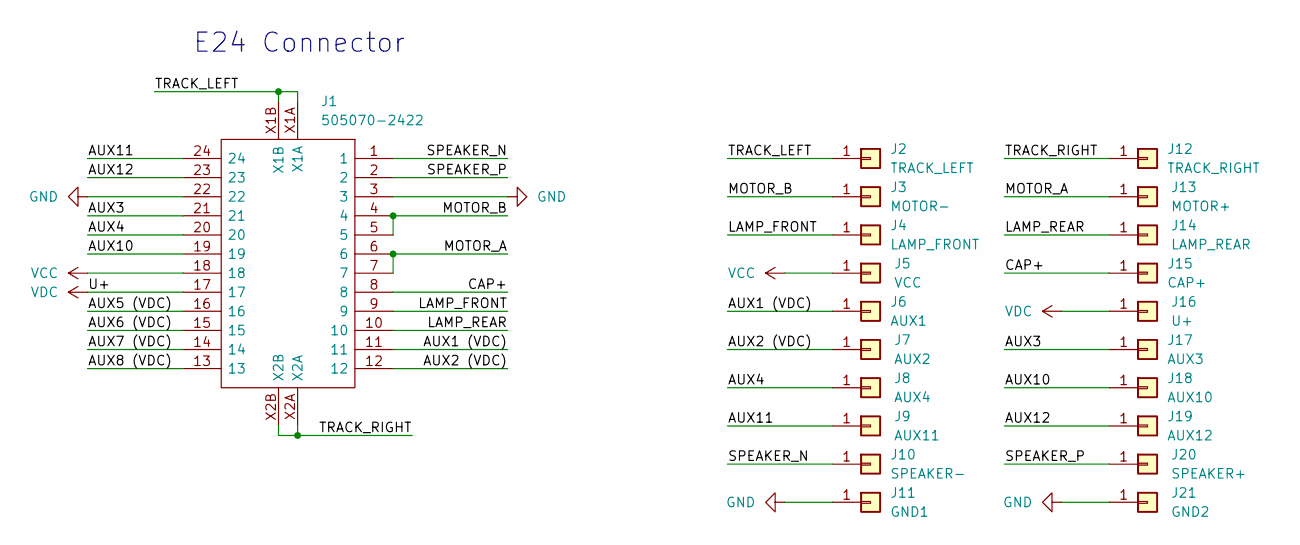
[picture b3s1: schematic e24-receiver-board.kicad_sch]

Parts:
J1: 505070-2422; CONN-SMD_24P-P0.35_5050702422; Manufacturer_Part_Number 505070-2422; LCSC C724143
J2: TRACK_LEFT; SolderWirePad_1x01_SMD_1.5x3mm
J3: MOTOR-; SolderWirePad_1x01_SMD_1.5x3mm
J4: LAMP_FRONT; SolderWirePad_1x01_SMD_1x2mm
J5: VCC; SolderWirePad_1x01_SMD_1x2mm
J6: AUX1; SolderWirePad_1x01_SMD_1x2mm
J7: AUX2; SolderWirePad_1x01_SMD_1x2mm
J8: AUX4; SolderWirePad_1x01_SMD_1x2mm
J9: AUX11; SolderWirePad_1x01_SMD_1x2mm
J10: SPEAKER-; SolderWirePad_1x01_SMD_1x2mm
J11: GND1; SolderWirePad_1x01_SMD_1.5x3mm
J12: TRACK_RIGHT; SolderWirePad_1x01_SMD_1.5x3mm
J13: MOTOR+; SolderWirePad_1x01_SMD_1.5x3mm
J14: LAMP_REAR; SolderWirePad_1x01_SMD_1x2mm
J15: CAP+; SolderWirePad_1x01_SMD_1x2mm
J16: U+; SolderWirePad_1x01_SMD_1x2mm
J17: AUX3; SolderWirePad_1x01_SMD_1x2mm
J18: AUX10; SolderWirePad_1x01_SMD_1x2mm
J19: AUX12; SolderWirePad_1x01_SMD_1x2mm
J20: SPEAKER+; SolderWirePad_1x01_SMD_1x2mm
J21: GND2; SolderWirePad_1x01_SMD_1.5x3mm

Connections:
/AUX1 (VDC): J1.11, J6.1
/AUX2 (VDC): J1.12, J7.1
/AUX3: J1.21, J17.1
/AUX4: J1.20, J8.1
/AUX5 (VDC): J1.16
/AUX6 (VDC): J1.15
/AUX7 (VDC): J1.14
/AUX8 (VDC): J1.13
/AUX10: J1.19, J18.1
/AUX11: J1.24, J9.1
/AUX12: J1.23, J19.1
/CAP+: J1.8, J15.1
/LAMP_FRONT: J1.9, J4.1
/LAMP_REAR: J1.10, J14.1
/MOTOR_A: J1.6, J1.7, J13.1
/MOTOR_B: J1.4, J1.5, J3.1
/SPEAKER_N: J1.1, J10.1
/SPEAKER_P: J1.2, J20.1
/TRACK_LEFT: J1.X1A, J1.X1B, J2.1
/TRACK_RIGHT: J1.X2A, J1.X2B, J12.1
GND: J1.3, J1.22, J11.1, J21.1
VCC: J1.18, J5.1
VDC: J1.17, J16.1

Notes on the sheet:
E24 Connector

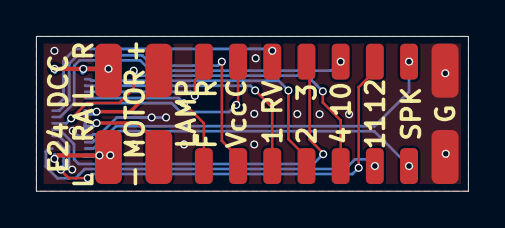
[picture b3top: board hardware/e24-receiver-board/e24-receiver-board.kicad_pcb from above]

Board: 2 copper layers, 24.0 x 8.6 mm, 21 parts (1 on the bottom side), 19 nets.
